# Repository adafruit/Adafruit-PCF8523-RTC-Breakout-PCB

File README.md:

## Adafruit PCF8523 RTC Breakout PCB

<a href="http://www.adafruit.com/products/5189"><br/>
Click here to purchase one from the Adafruit shop</a>

<a href="http://www.adafruit.com/products/3295"><br/>
Click here to purchase one from the Adafruit shop</a>

PCB files for the Adafruit PCF8523 RTC Breakout. Format is EagleCAD schematic and board layout

For more details, check out the product pages at
* https://www.adafruit.com/products/3295

### Description

This is a great battery-backed real time clock (RTC) that allows your microcontroller project to keep track of time even if it is reprogrammed, or if the power is lost. Perfect for datalogging, clock-building, time stamping, timers and alarms, etc. Equipped with PCF8523 RTC - it can run from 3.3V or 5V power & logic!

Works great with an Arduino using our RTC library, with CircuitPython or with a Raspberry Pi (or similar single board linux computer)

* PCB & header are included
* Plugs into any breadboard, or you can use wires
* Two mounting holes
* Will keep time for 5 years or more

**Note: This product does not come with a CR1220 coin cell battery. We recommend you purchase a coin cell battery to use with this product.**

The PCF8523 is simple and inexpensive but not a high precision device. It may lose or gain up to 2 seconds a day. For a high-precision, temperature compensated alternative, please check out the DS3231 precision RTC. If you need a DS1307 for compatibility reasons, check out our DS1307 RTC breakout

### License

Adafruit invests time and resources providing this open source design, please support Adafruit and open-source hardware by purchasing products from [Adafruit](https://www.adafruit.com)!

Designed by Limor Fried/Ladyada for Adafruit Industries.

Creative Commons Attribution/Share-Alike, all text above must be included in any redistribution. See license.txt for additional details.

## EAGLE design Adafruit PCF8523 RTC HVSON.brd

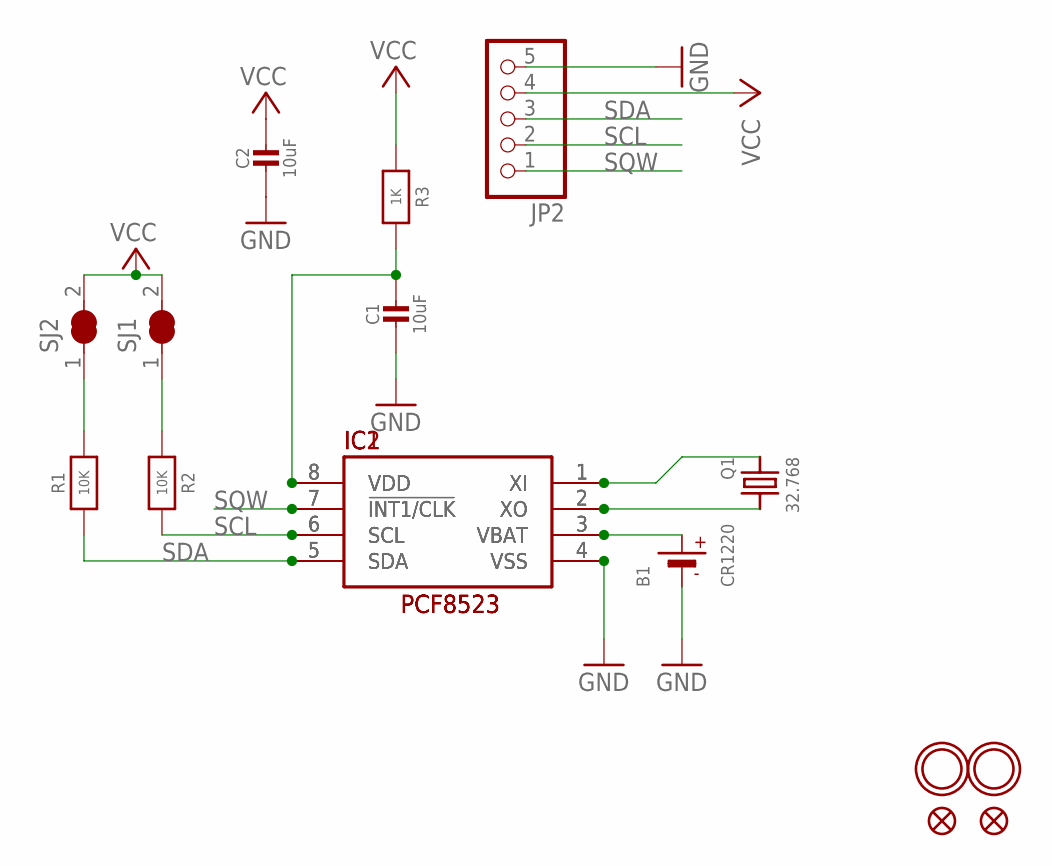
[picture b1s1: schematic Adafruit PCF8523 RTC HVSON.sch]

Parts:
B1: CR1220
C1, C2: 10uF; 0805-NO
FID1, FID2: FIDUCIAL_1MM
IC1: RTC_PCF8523/T; SOIC8_150MIL
IC2: RTC_PCF8523/TK; HVSON8_4X4
JP2: HEADER-1X576MIL; 1X05_ROUND_76
Q1: 32.768; XTAL3215
R1, R2: 10K; 0805-NO
R3: 1K; 0805-NO
SJ1, SJ2: SOLDERJUMPER_CLOSED; SOLDERJUMPER_CLOSEDWIRE
U$1, U$4: MOUNTINGHOLE2.0; MOUNTINGHOLE_2.0_PLATED

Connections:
GND: B1.-, C1.2, C2.2, IC1.4 (VSS), IC2.4 (VSS), JP2.5
unnamed: R2.1, SJ1.1
unnamed: R1.2, SJ2.1
unnamed: C1.1, IC1.8 (VDD), IC2.8 (VDD), R3.2
unnamed: IC1.1 (XI), IC2.1 (XI), Q1.P$1 (1)
unnamed: IC1.2 (XO), IC2.2 (XO), Q1.P$2 (2)
SCL: IC1.6 (SCL), IC2.6 (SCL), JP2.2, R2.2
SDA: IC1.5 (SDA), IC2.5 (SDA), JP2.3, R1.1
SQW: IC1.7 (!INT1/CLK), IC2.7 (!INT1/CLK), JP2.1
VBAT: B1.+$1 (+), B1.+$2 (+), IC1.3 (VBAT), IC2.3 (VBAT)
VCC: C2.1, JP2.4, R3.1, SJ1.2, SJ2.2

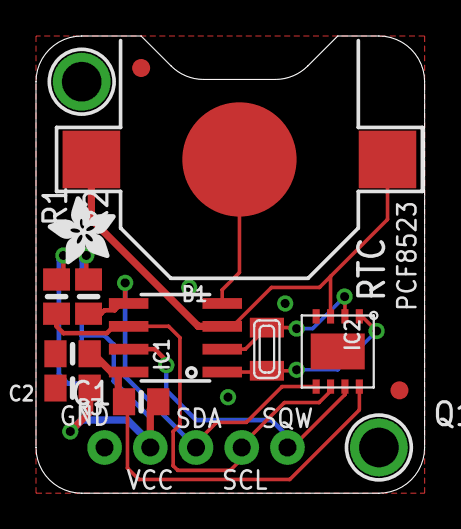
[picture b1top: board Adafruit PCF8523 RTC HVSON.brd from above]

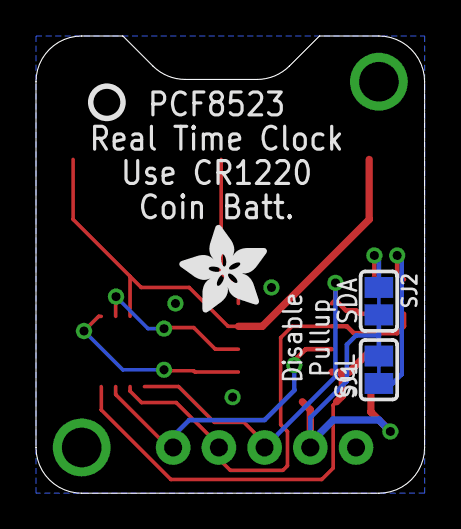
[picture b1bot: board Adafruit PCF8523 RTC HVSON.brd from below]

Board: 2 copper layers, 21.6 x 25.4 mm, 19 parts (4 on the bottom side), 11 nets.

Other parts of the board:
U$2: ADAFRUIT_3.5MM
U$3: PCBFEAT-REV-040
U$5: ADAFRUIT_5MM

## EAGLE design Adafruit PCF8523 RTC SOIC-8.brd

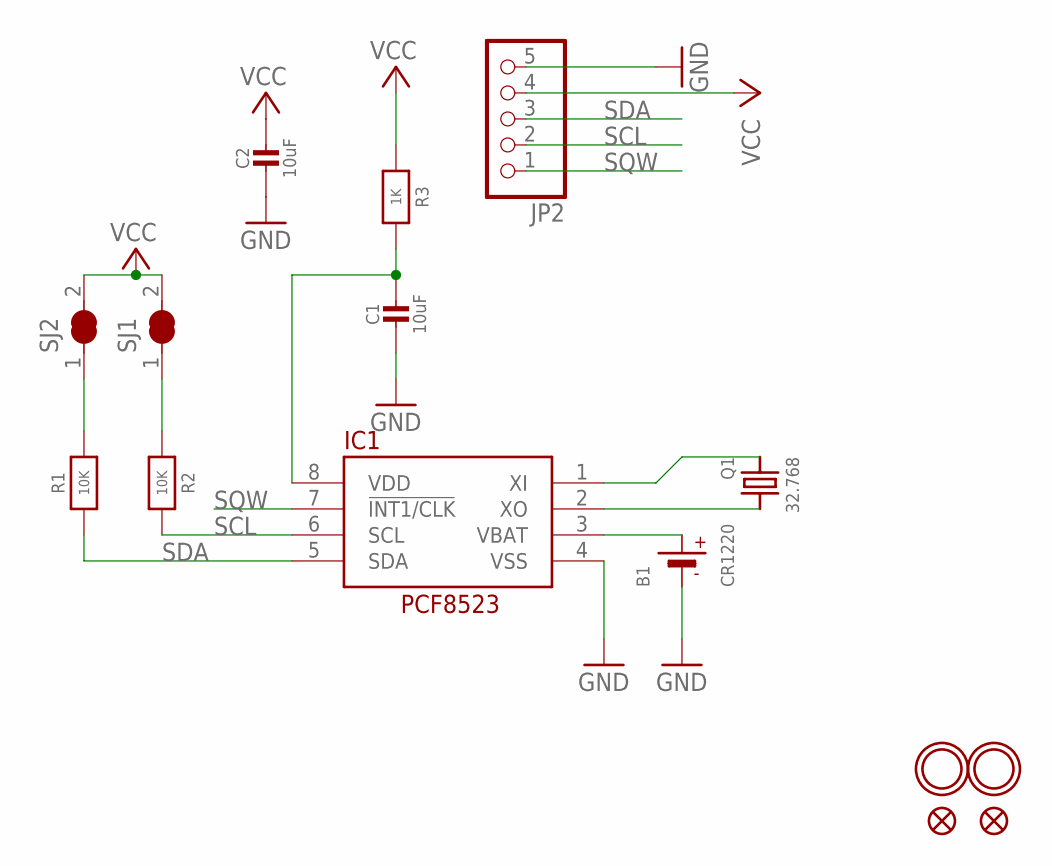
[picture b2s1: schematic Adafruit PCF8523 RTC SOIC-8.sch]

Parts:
B1: CR1220
C1, C2: 10uF; 0805-NO
FID1, FID2: FIDUCIAL""; FIDUCIAL_1MM
IC1: RTC_PCF8523T; SOIC8_150MIL
JP2: HEADER-1X576MIL; 1X05_ROUND_76
Q1: 32.768; CRYSTAL_8X3.8
R1, R2: 10K; 0805-NO
R3: 1K; 0805-NO
SJ1, SJ2: SOLDERJUMPER_CLOSED; SOLDERJUMPER_CLOSEDWIRE
U$1, U$4: MOUNTINGHOLE2.0; MOUNTINGHOLE_2.0_PLATED

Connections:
GND: B1.-, C1.2, C2.2, IC1.4 (VSS), JP2.5
unnamed: R2.1, SJ1.1
unnamed: R1.2, SJ2.1
unnamed: C1.1, IC1.8 (VDD), R3.2
unnamed: IC1.1 (XI), Q1.P$1 (1)
unnamed: IC1.2 (XO), Q1.P$4 (2)
SCL: IC1.6 (SCL), JP2.2, R2.2
SDA: IC1.5 (SDA), JP2.3, R1.1
SQW: IC1.7 (!INT1/CLK), JP2.1
VBAT: B1.+$1 (+), IC1.3 (VBAT)
VCC: C2.1, JP2.4, R3.1, SJ1.2, SJ2.2

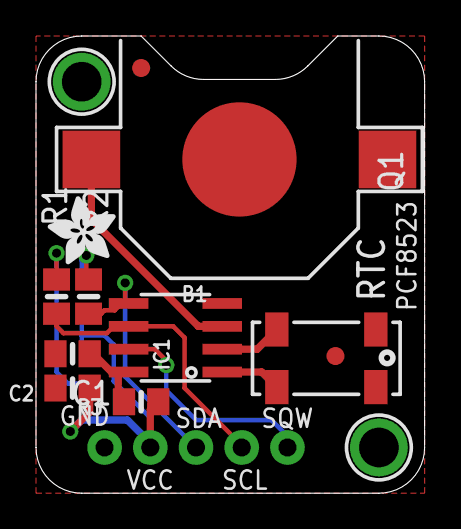
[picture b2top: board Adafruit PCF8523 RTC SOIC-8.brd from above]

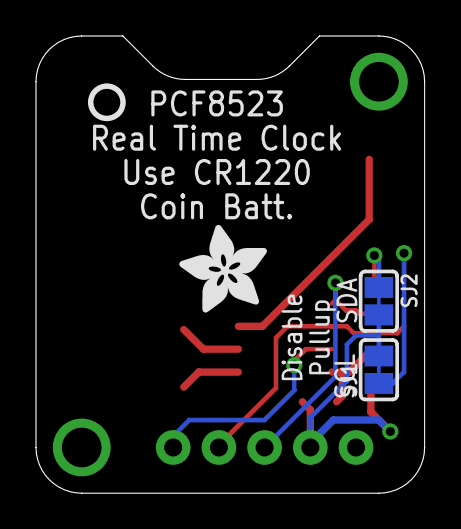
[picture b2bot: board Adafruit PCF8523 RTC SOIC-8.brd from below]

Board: 2 copper layers, 21.6 x 25.4 mm, 18 parts (4 on the bottom side), 11 nets.

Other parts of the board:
U$2: ADAFRUIT_3.5MM
U$3: PCBFEAT-REV-040
U$5: ADAFRUIT_5MM

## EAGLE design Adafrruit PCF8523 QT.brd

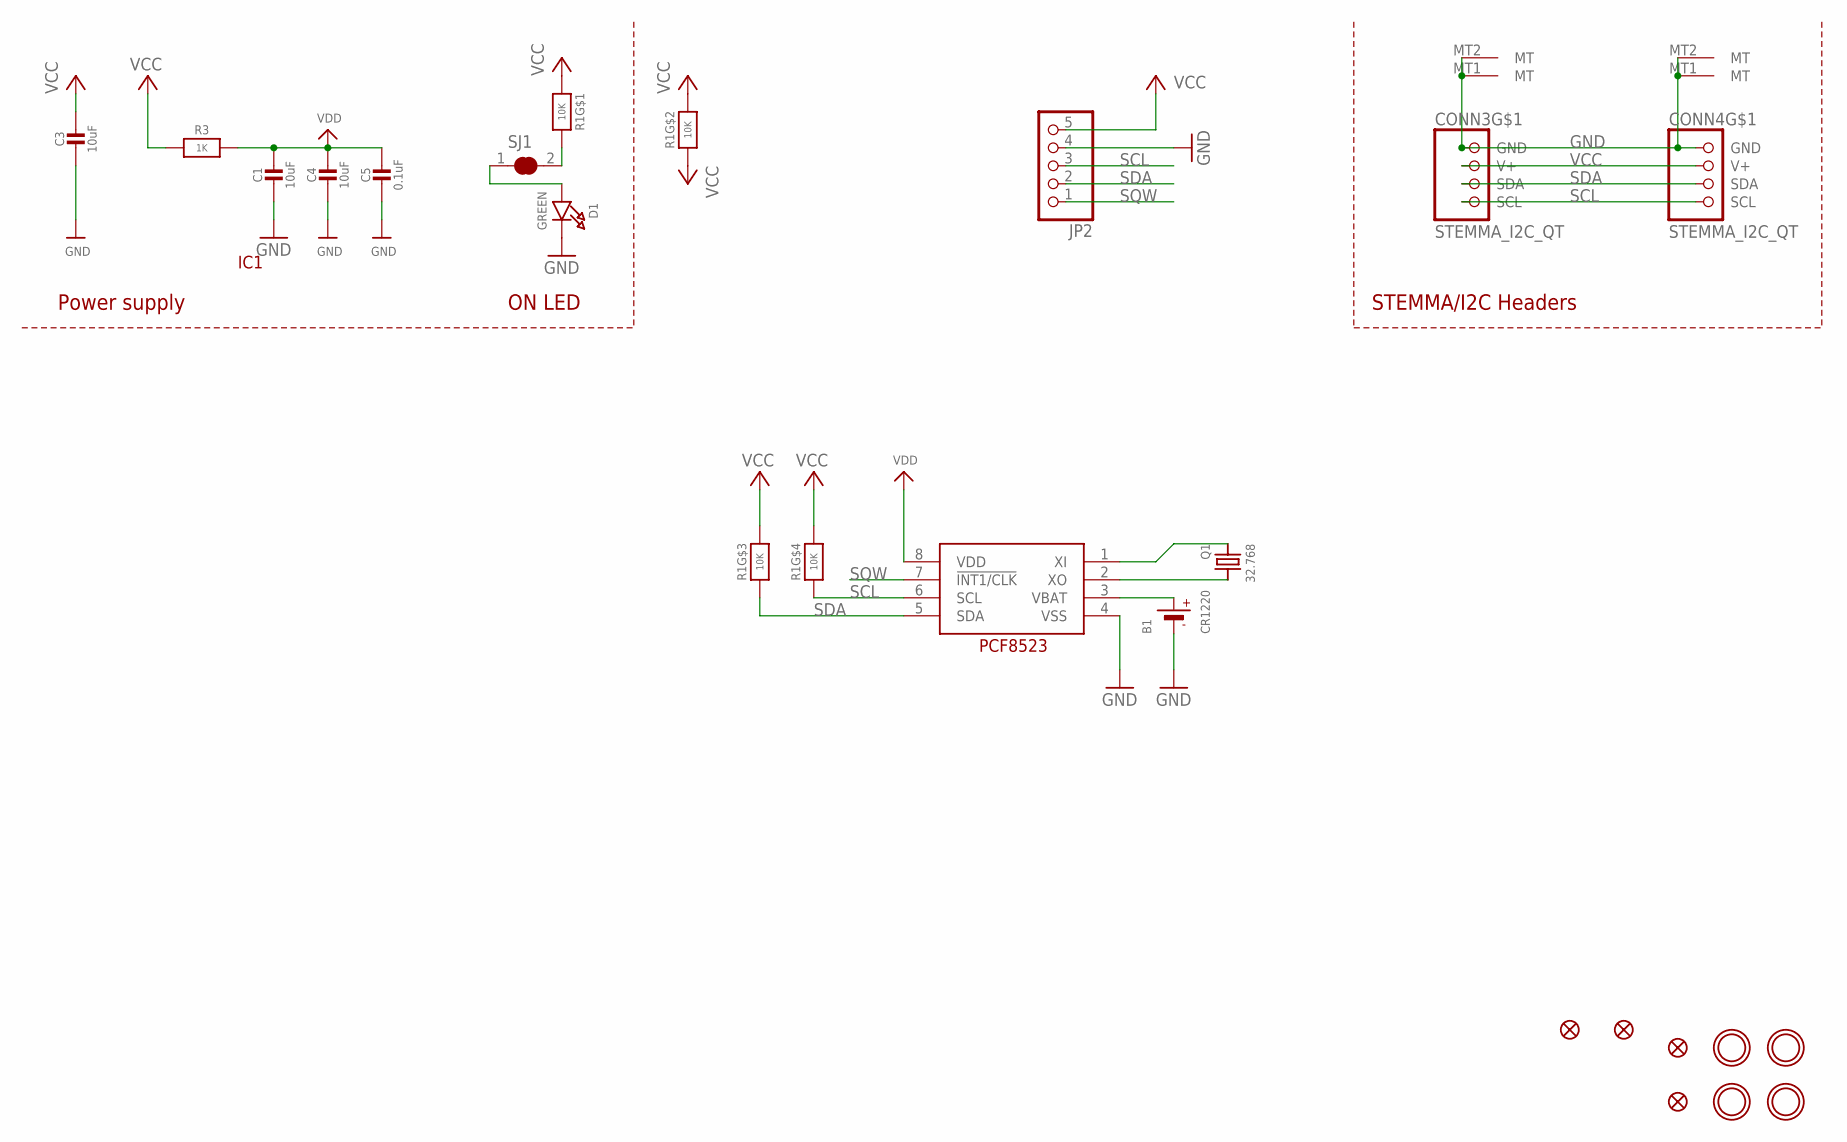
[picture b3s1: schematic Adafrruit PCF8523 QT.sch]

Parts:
B1: CR1220
C1, C3, C4: 10uF; 0805-NO
C5: 0.1uF; 0603-NO
CONN3, CONN4: STEMMA_I2C_QT; JST_SH4
D1: GREEN; CHIPLED_0603_NOOUTLINE
FID1, FID2, FID3, FID4: FIDUCIAL_1MM
IC1: RTC_PCF8523T; SOIC8_150MIL
JP2: HEADER-1X570MIL; 1X05_ROUND_70
Q1: 32.768; XTAL3215
R1: 10K; RESPACK_4X0603
R3: 1K; 0603-NO
SJ1: SOLDERJUMPER_CLOSED; SOLDERJUMPER_CLOSEDWIRE
U$9, U$17, U$19, U$21: MOUNTINGHOLE3.0THIN; MOUNTINGHOLE_3.0_PLATEDTHIN

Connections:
GND: B1.-, C1.2, C3.2, C4.2, C5.2, CONN3.1 (GND), CONN3.MT1 (MT), CONN3.MT2 (MT), CONN4.1 (GND), CONN4.MT1 (MT), CONN4.MT2 (MT), D1.C, IC1.4 (VSS), JP2.4
unnamed: R1.8 (2), SJ1.2
unnamed: D1.A, SJ1.1
unnamed: IC1.1 (XI), Q1.P$1 (1)
unnamed: IC1.2 (XO), Q1.P$2 (2)
SCL: CONN3.4 (SCL), CONN4.4 (SCL), IC1.6 (SCL), JP2.3, R1.4 (1)
SDA: CONN3.3 (SDA), CONN4.3 (SDA), IC1.5 (SDA), JP2.2, R1.3 (1)
SQW: IC1.7 (!INT1/CLK), JP2.1
VBAT: B1.+$1 (+), B1.+$2 (+), IC1.3 (VBAT)
VCC: C3.1, CONN3.2 (V+), CONN4.2 (V+), JP2.5, R1.1, R1.2 (1), R1.5 (2), R1.6 (2), R1.7 (2), R3.1
VDD: C1.1, C4.1, C5.1, IC1.8 (VDD), R3.2

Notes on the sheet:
STEMMA/I2C Headers
ON LED
Power supply

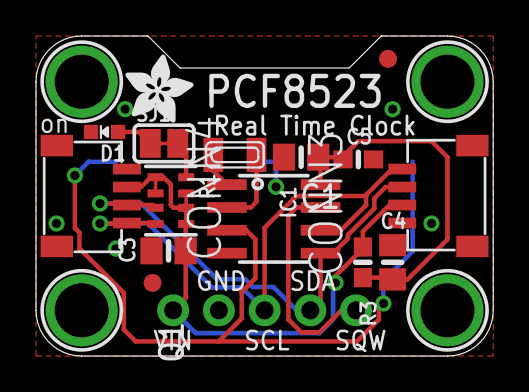
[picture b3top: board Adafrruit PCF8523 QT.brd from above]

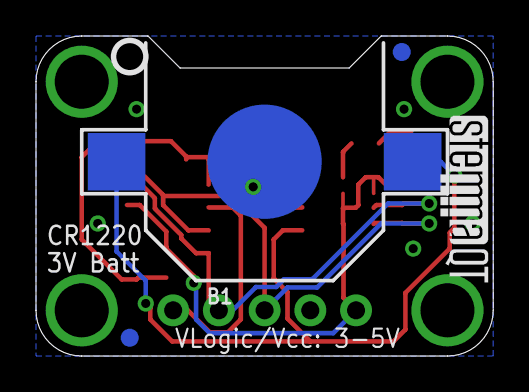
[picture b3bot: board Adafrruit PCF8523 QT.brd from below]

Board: 2 copper layers, 25.4 x 17.8 mm, 25 parts (5 on the bottom side), 11 nets.

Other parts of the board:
U$22: ADAFRUIT_3.5MM
U$25: PCBFEAT-REV-040
U$31: STEMMAQT

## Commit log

2017-06-14 commit!
2018-05-07 https://github.com/adafruit/Adafruit-PCF8523-RTC-Breakout-PCB/issues/1
2021-08-03 Add QT board files.
2021-08-03 Add asset.
2022-04-13 Update board files.

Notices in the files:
parts and their libraries:
microbuilder: This work is placed in the public domain, and may be freely used for commercial and non-commercial work with the following conditions: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
